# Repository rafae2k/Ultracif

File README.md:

</br>

### O UltraCif é um equipamento de descontaminação de máscaras através de luz ultravioleta para reutilização rápida e segura. Ele foi desenvolvido para amparar profissionais da saúde na luta contra a pandemia do COVID-19.

##### 1 - [Bibliografia](https://github.com/rafae2k/Ultracif/tree/main/Bibliografia)

  ###### Nesta seção você encontrará os principais artigos utilizados para pesquisa e desenvolvimento do Ultracif.

##### 1.1 - [Datasheet](https://github.com/rafae2k/Ultracif/tree/main/Datasheet)
  
  ###### Nesta seção você encontrará os datasheets dos principais componentes utilizados no Ultracif.

##### 2 - [Dosimetria](https://github.com/rafae2k/Ultracif/tree/main/Dosimetria)
  
  ###### Nesta seção é apresentado o programa elaborado em MATLAB para geração dos dados e graficos de irradiancia baseados nos dados da fabricante de lâmpadas UVC OSRAM.

##### 3 - [CAD](https://github.com/rafae2k/Ultracif/tree/main/CAD)

  ###### Nesta seção você encontrará os arquivos 3D dos componentes do Ultracif.

##### 4 [Eletroeletronica](https://github.com/rafae2k/Ultracif/tree/main/Eletroeletronica)
  
  ###### Nesta seção você encontrará os arquivos relativos ao desenvolvimento do PCB da placa controladora e diagrama do circuito elétrico.

 ##### 4.1 - [Firmware](https://github.com/rafae2k/Ultracif/tree/main/Eletroeletronica/Firmware)
   
   ###### Nesta seção você encontrará os arquivos do código-fonte utilizados no firmware do Ultracif.
  
##### 5 - [Lista de Materiais](https://github.com/rafae2k/Ultracif/tree/main/Lista%20de%20Materiais)
   
   ###### Nesta seção você encontrará a lista com todos os materiais utilizados para montagem do Ultracif.

##### 6 - [Orientações Gerais](https://github.com/rafae2k/Ultracif/tree/main/Orienta%C3%A7%C3%B5es)
   
   ###### Nesta seção você encontrará todas as orientações necessárias para operação do equipamento.

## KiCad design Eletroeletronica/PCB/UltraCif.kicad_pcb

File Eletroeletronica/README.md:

# ELETROELETRONICA
  ###### Nesta seção você encontrará os arquivos relativos ao desenvolvimento da placa controladora e diagrama do circuito elétrico.

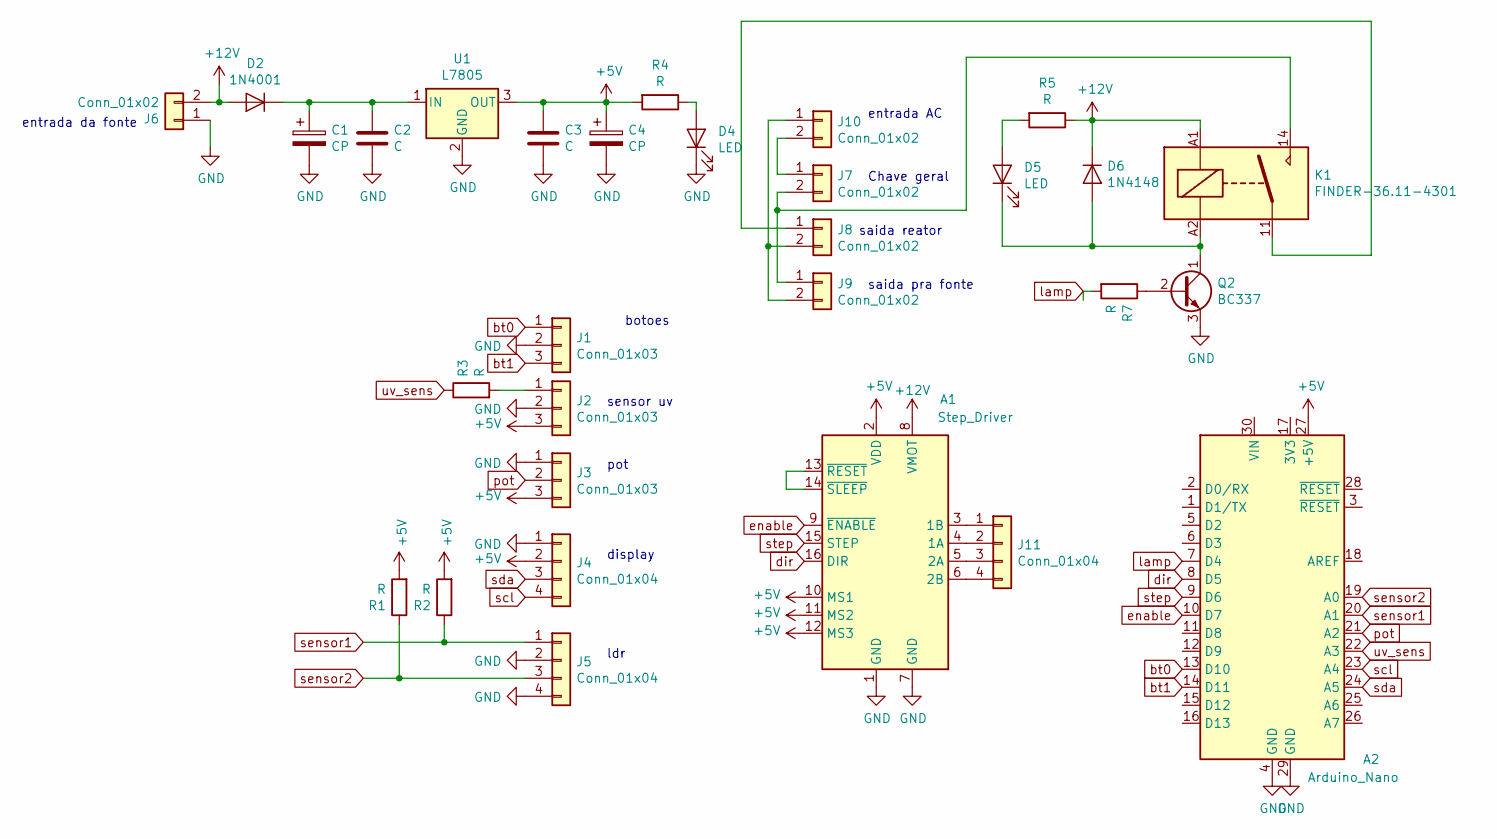
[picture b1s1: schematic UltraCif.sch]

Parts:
A1: Step_Driver; Pololu_Breakout-16_15.2x20.3mm
A2: Arduino_Nano
C1, C4: CP; CP_Radial_D10.0mm_P5.00mm
C2, C3: C; C_Disc_D5.0mm_W2.5mm_P5.00mm
D2: 1N4001; D_DO-41_SOD81_P10.16mm_Horizontal
D4, D5: LED; LED_D3.0mm
D6: 1N4148; D_DO-35_SOD27_P7.62mm_Horizontal
J1, J2, J3: Conn_01x03; PinHeader_1x03_P2.54mm_Vertical
J4, J5, J11: Conn_01x04; PinHeader_1x04_P2.54mm_Vertical
J6, J7, J8, J9, J10: Conn_01x02; TerminalBlock_bornier-2_P5.08mm
K1: FINDER-36.11-4301; Relay_SPDT_Finder_36.11
Q2: BC337; TO-92_Inline_Wide
R1, R2, R3, R4, R5, R7: R; R_Axial_DIN0207_L6.3mm_D2.5mm_P7.62mm_Horizontal
U1: L7805; TO-220-3_Vertical

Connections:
+5V: A1.2 (VDD), A1.10 (MS1), A1.11 (MS2), A1.12 (MS3), A2.27 (+5V), C3.1, C4.1, J2.3, J3.3, J4.2, R1.2, R2.2, R4.2, U1.3 (OUT)
+12V: A1.8 (VMOT), D2.2 (A), D6.1 (K), J6.2, K1.A1, R5.1
GND: A1.1 (GND), A1.7 (GND), A2.4 (GND), A2.29 (GND), C1.2, C2.2, C3.2, C4.2, D4.1 (K), J1.2, J2.2, J3.1, J4.1, J5.2, J5.4, J6.1, Q2.3 (E), U1.2 (GND)
unnamed: A1.3 (1B), J11.1
unnamed: A1.4 (1A), J11.2
unnamed: A1.5 (2A), J11.3
unnamed: A1.6 (2B), J11.4
unnamed: A1.13 (~RESET), A1.14 (~SLEEP)
unnamed: C1.1, C2.1, D2.1 (K), U1.1 (IN)
unnamed: D4.2 (A), R4.1
unnamed: D5.1 (K), D6.2 (A), K1.A2, Q2.1 (C)
unnamed: D5.2 (A), R5.2
unnamed: J2.1, R3.2
unnamed: J7.2, J9.1, K1.14
unnamed: J8.1, K1.11
unnamed: J8.2, J9.2, J10.1
unnamed: J7.1, J10.2
unnamed: Q2.2 (B), R7.1
bt0: A2.13 (D10), J1.1
bt1: A2.14 (D11), J1.3
dir: A1.16 (DIR), A2.8 (D5)
enable: A1.9 (~ENABLE), A2.10 (D7)
lamp: A2.7 (D4), R7.2
pot: A2.21 (A2), J3.2
scl: A2.23 (A4), J4.4
sda: A2.24 (A5), J4.3
sensor1: A2.20 (A1), J5.1, R2.1
sensor2: A2.19 (A0), J5.3, R1.1
step: A1.15 (STEP), A2.9 (D6)
uv_sens: A2.22 (A3), R3.1

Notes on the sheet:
entrada AC
Chave geral
saida reator
saida pra fonte
entrada da fonte
botoes
sensor uv
pot
display
ldr

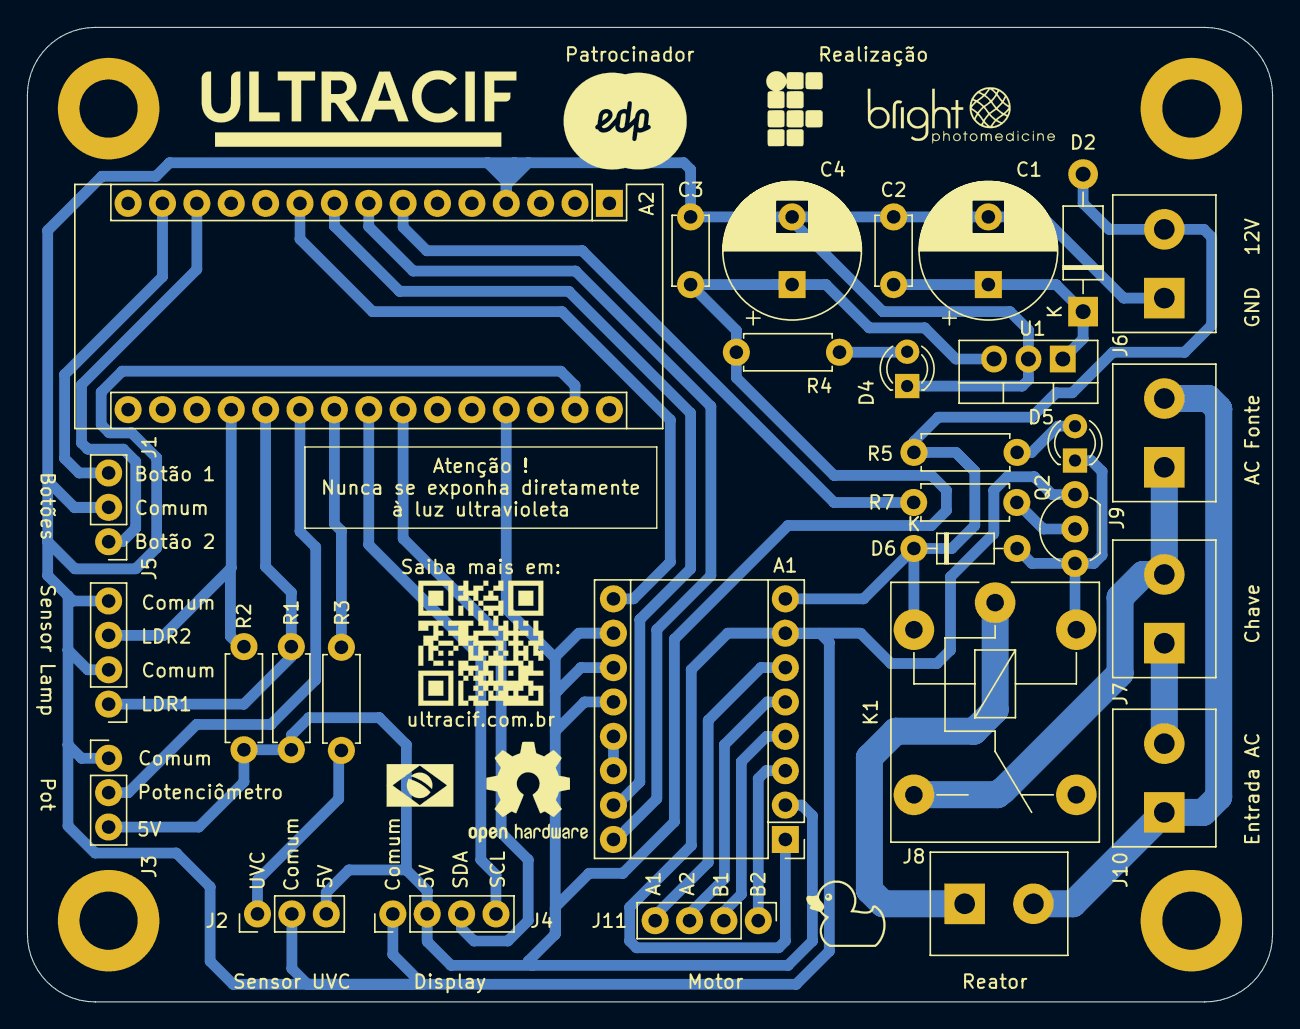
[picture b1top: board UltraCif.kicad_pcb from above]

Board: 2 copper layers, 92.0 x 72.0 mm, 30 parts (0 on the bottom side), 30 nets.

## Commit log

2020-10-12 Set theme jekyll-theme-cayman
2020-11-21 COPYRIGHT
2020-11-21 DELETE
